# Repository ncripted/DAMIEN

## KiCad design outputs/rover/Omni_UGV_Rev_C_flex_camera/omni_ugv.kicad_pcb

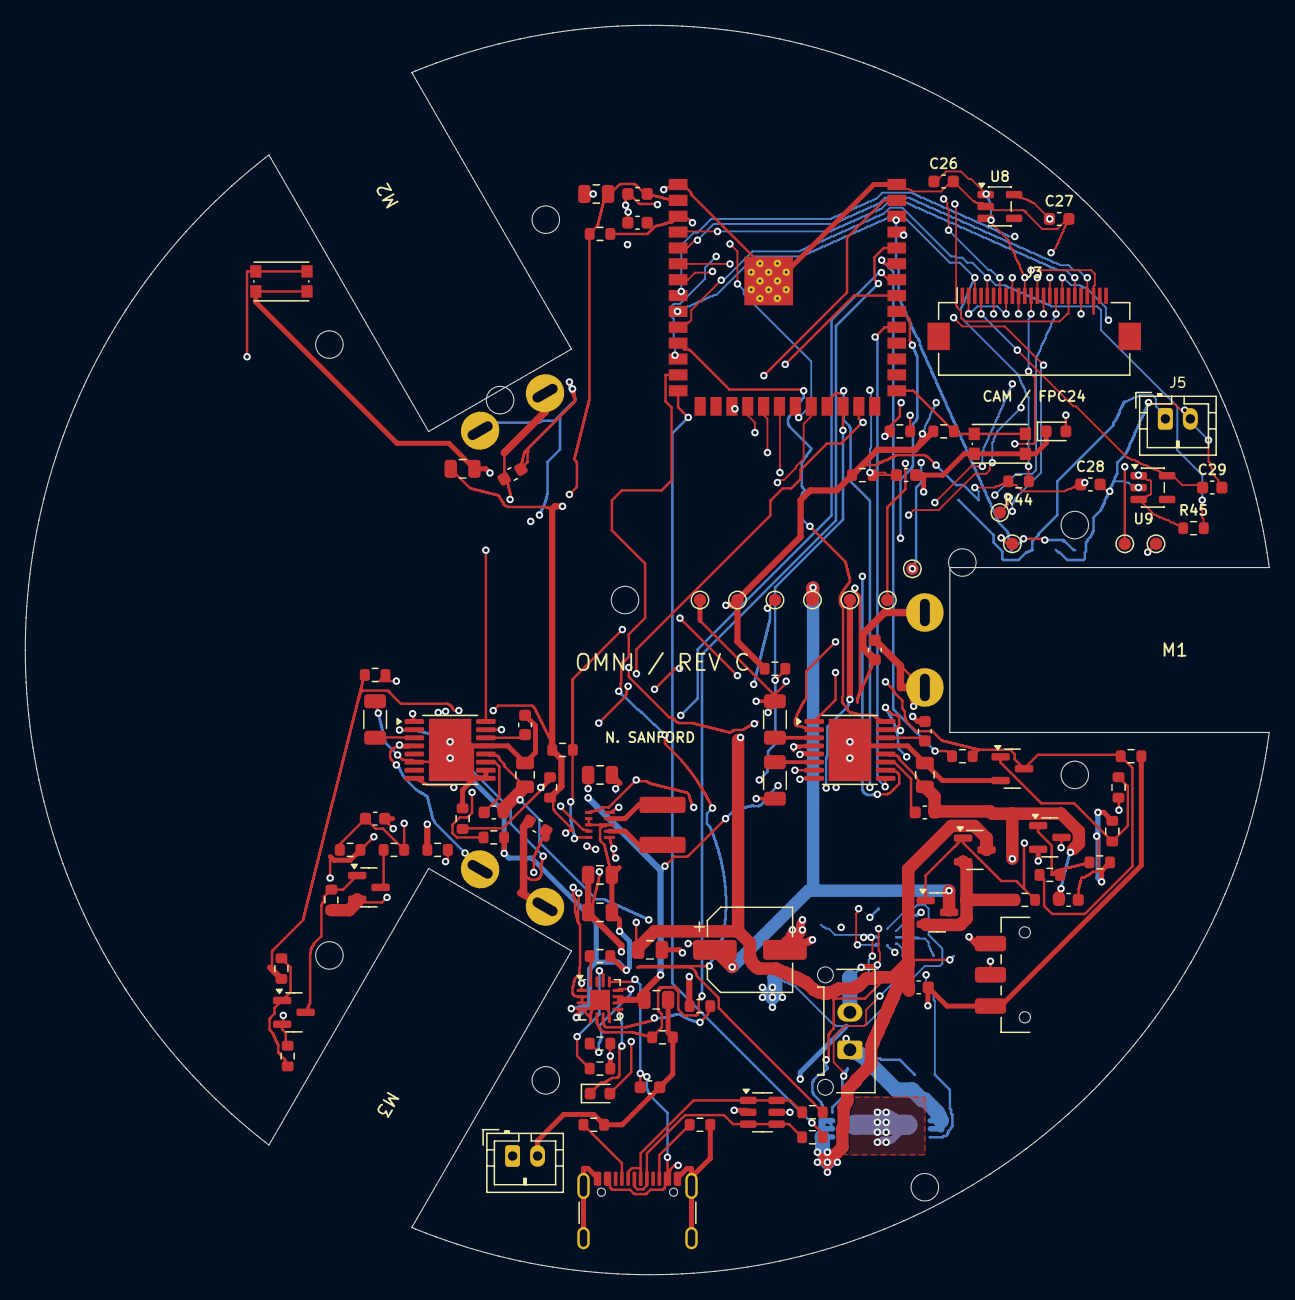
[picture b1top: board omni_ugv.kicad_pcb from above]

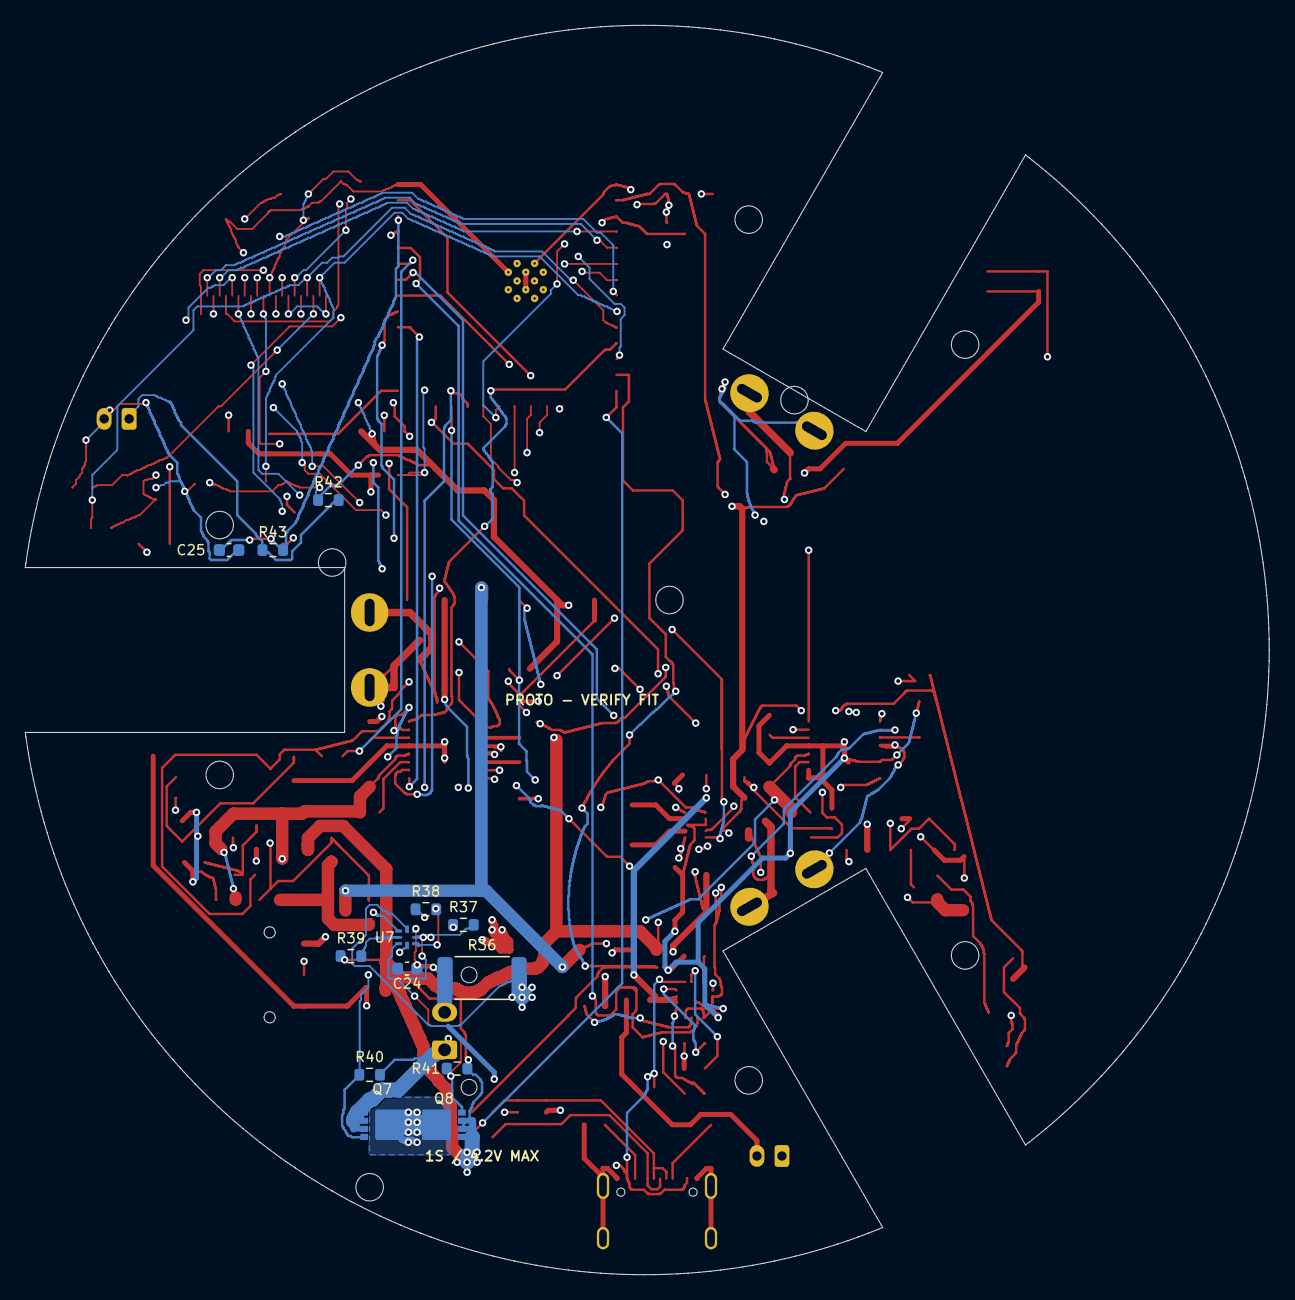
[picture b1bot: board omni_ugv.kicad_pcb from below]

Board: 4 copper layers, 99.6 x 100.0 mm, 127 parts (13 on the bottom side), 87 nets.

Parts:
C1, C15, C21: 1u/10V; Capacitor_SMD__C_0603_1608Metric
C2, C5, C6, C9, C16, C17, C18: 10u/10V; Capacitor_SMD__C_0805_2012Metric
C3, C4, C22, C23: 100n/16V; Capacitor_SMD__C_0603_1608Metric
C7, C10: 2.2u/10V; Capacitor_SMD__C_0603_1608Metric
C8, C11: 10n/25V; Capacitor_SMD__C_0603_1608Metric
C12, C13, C14: 100n/25V; Capacitor_SMD__C_0603_1608Metric
C19, C20: 22u/10V; Capacitor_SMD__C_0805_2012Metric
C24, C25: 100n/16V X7R; Capacitor_SMD__C_0603_1608Metric
C26, C27, C28, C29: 2.2u/10V X7R; Capacitor_SMD__C_0603_1608Metric
C90: 220u/10V; CP_Elec_6.3x5.8_HandAssembly
D1: STATUS GREEN; LED_SMD__LED_0603_1608Metric
D2: CHARGE AMBER; LED_SMD__LED_0603_1608Metric
H1, H2, H3, H4, H5, H6, H7, H8, H9, H10: M2; MountingHole_2.2mm_M2
J1: USB-C; Connector_USB__USB_C_Receptacle_GCT_USB4105-xx-A_16P_TopMnt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
J2: RAW 1S CELL 4.2V MAX; Connector_Molex__Molex_Micro-Fit_3.0_43650-0215_1x02_P3.00m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
J3: M0031 CAMERA FPC24; Camera_FH12_24
J4: CELL NTC - CHARGER; Connector_JST__JST_PH_B2B-PH-K_1x02_P2.00mm_Vertical
J5: CELL NTC - DRIVE; Connector_JST__JST_PH_B2B-PH-K_1x02_P2.00mm_Vertical
L1: 0.47uH/5.4A; L_XFL4015
M1: POLOLU 3065 MOTOR 1; Pololu_HPCB_Solder
M2: POLOLU 3065 MOTOR 2; Pololu_HPCB_Solder
M3: POLOLU 3065 MOTOR 3; Pololu_HPCB_Solder
Q1, Q2, Q5: AO3401A; Package_TO_SOT_SMD__SOT-23
Q3, Q4, Q6: MMBT3904; Package_TO_SOT_SMD__SOT-23
Q7, Q8: CSD17308Q3; CSD17308Q3_TI
R1, R2, R4, R5, R8, R29: 10k; Resistor_SMD__R_0603_1608Metric
R3, R27: 1k; Resistor_SMD__R_0603_1608Metric
R6, R7, R9: 0.25R/0.5W; Resistor_SMD__R_1206_3216Metric
R10, R11: 5.1k; Resistor_SMD__R_0603_1608Metric
R12, R13: 22R; Resistor_SMD__R_0603_1608Metric
R14: 3.57k; Resistor_SMD__R_0603_1608Metric
R15: 3.24k; Resistor_SMD__R_0603_1608Metric
R16: 46.4k; Resistor_SMD__R_0603_1608Metric
R17, R19, R22, R23, R24, R25, R26, R28, R30, R31, R33, R34, R35: 100k; Resistor_SMD__R_0603_1608Metric
R18: 2.2k; Resistor_SMD__R_0603_1608Metric
R20: 511k; Resistor_SMD__R_0603_1608Metric
R21: 91k; Resistor_SMD__R_0603_1608Metric
R32: 47k; Resistor_SMD__R_0603_1608Metric
R36: 10m 1% 1W; Resistor_SMD__R_2512_6332Metric
R37: 100R 1%; Resistor_SMD__R_0603_1608Metric
R38: 20R 1%; Resistor_SMD__R_0603_1608Metric
R39, R43: 1k 1%; Resistor_SMD__R_0603_1608Metric
R40, R41: 10M; Resistor_SMD__R_0603_1608Metric
R42: 10k 1%; Resistor_SMD__R_0603_1608Metric
R44, R45: 4.7k; Resistor_SMD__R_0603_1608Metric
SW1: RESET; Button_Switch_SMD__SW_Push_1P1T_NO_CK_KMR2
SW2: BOOT; Button_Switch_SMD__SW_Push_1P1T_NO_CK_KMR2
SW3: POWER; Button_Switch_SMD__SW_SPDT_CK_JS102011SAQN
TP1: GND; TestPoint__TestPoint_Pad_D1.0mm
TP2: +3V3; TestPoint__TestPoint_Pad_D1.0mm
TP3: VBAT; TestPoint__TestPoint_Pad_D1.0mm
TP4: VMOTOR; TestPoint__TestPoint_Pad_D1.0mm
TP5: SYS_RAW; TestPoint__TestPoint_Pad_D1.0mm
TP6: ESP_EN; TestPoint__TestPoint_Pad_D1.0mm
TP7: LED_STATUS; TestPoint__TestPoint_Pad_D1.0mm
TP8: DRIVE_ENABLE; TestPoint__TestPoint_Pad_D1.0mm
TP9: FAULT_U2; TestPoint__TestPoint_Pad_D1.0mm
TP10: FAULT_U3; TestPoint__TestPoint_Pad_D1.0mm
TP11: REG_PG; TestPoint__TestPoint_Pad_D1.0mm
U1: ESP32-S3-WROOM-1-N8R8; RF_Module__ESP32-S3-WROOM-1
U2, U3: DRV8833PWP; Package_SO__HTSSOP-16-1EP_4.4x5mm_P0.65mm_EP3.4x5mm_Mask2.4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
U4: TPS63802DLA; TPS63802_DLA0010A
U5: BQ24074RGT; Package_DFN_QFN__VQFN-16-1EP_3x3mm_P0.5mm_EP1.6x1.6mm
U6: USBLC6-2SC6; Package_TO_SOT_SMD__SOT-23-6
U7: BQ298217RUGR; BQ298217_RUG0008A
U8: TLV75513PDBVR; Camera_SOT23_5
U9: TLV75528PDBVR; Camera_SOT23_5

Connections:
+3V3: C2.1, C3.1, C5.1, C19.1, C20.1, C26.1, C28.1, J3.11, R1.1, R2.1, R4.1, R5.1, R8.1, R19.1, R20.1, R22.1, R32.1, R42.1, R44.1, R45.1, TP2.1, U1.2, U4.6, U8.1, U8.3, U9.1, U9.3
BAT_NTC: J4.1, U5.1
CAM_1V3: C27.1, J3.10, U8.5
CAM_2V8: C29.1, J3.4, U9.5
CAM_D0: J3.19, U1.4
CAM_D1: J3.21, U1.5
CAM_D2: J3.22, U1.6
CAM_D3: J3.20, U1.7
CAM_D4: J3.18, U1.12
CAM_D5: J3.16, U1.17
CAM_D6: J3.14, U1.18
CAM_D7: J3.12, U1.19
CAM_HREF: J3.9, U1.22
CAM_PCLK: J3.17, U1.20
CAM_RESET: C4.1, J3.6, R4.2
CAM_SCL: J3.5, R45.2, U1.10
CAM_SDA: J3.3, R44.2, U1.9
CAM_VSYNC: J3.7, U1.21
CAM_XCLK: J3.13, U1.8
CELL_N: C24.2, J2.2, R36.1, U7.3, U7.5
CELL_P: J2.1, Q7.1, Q7.2, Q7.3, R37.1, R38.1, R40.2
CELL_TEMP_ADC: C25.1, R43.2, U1.38
CELL_TEMP_DIV: J5.1, R42.2, R43.1
CHG_ILIM: R15.1, U5.12
CHG_ISET: R14.1, U5.16
CHG_LED_A: D2.2, R18.2
CHG_PGOOD: R19.2, U5.7
CHG_STATUS: D2.1, U5.9
CHG_TIMER: R16.1, U5.14
DRIVE_ENABLE: Q4.3, R25.1, R27.2, R28.1, TP8.1, U2.1, U3.1
DRIVE_REQ: R27.1, U1.35
ESP_BOOT: R2.2, SW2.1, U1.27
ESP_EN: C1.1, R1.2, SW1.1, TP6.1, U1.3
FAULT_U2: R5.2, TP9.1, U1.24, U2.8
FAULT_U3: R8.2, TP10.1, U1.25, U3.8
GND: C1.2, C2.2, C3.2, C4.2, C5.2, C6.2, C7.2, C9.2, C10.2, C15.2, C16.2, C17.2, C18.2, C19.2, C20.2, C21.2, C22.2, C23.2, C25.2, C26.2, C27.2, C28.2, C29.2, C90.2, D1.1, J1.A1, J1.A12, J1.B1, J1.B12, J1.S1, J3.2, J3.8, J3.15, J4.2, J5.2, Q3.2, Q4.2, Q6.2, R6.2, R7.2, R9.2, R10.2, R11.2, R14.2, R15.2, R16.2, R17.2, R21.2, R23.2, R26.2, R28.2, R30.2, R33.2, R35.2, R36.2, SW1.2, SW2.2, SW3.1, TP1.1, U1.1, U1.40, U1.41, U2.13, U2.17, U3.6, U3.9, U3.10, U3.13, U3.17, U4.2, U4.3, U4.8, U5.4, U5.5, U5.8, U5.17, U6.2, U7.4, U8.2, U9.2
LED_A: D1.2, R3.2
LED_STATUS: R3.1, TP7.1, U1.37
M1_A: C12.1, M1.1, U2.2
M1_B: C12.2, M1.2, U2.4
M1_IN1: U1.11, U2.16
M1_IN2: U1.23, U2.15
M1_SENSE: R6.1, U2.3
M2_A: C13.1, M2.1, U2.7
M2_B: C13.2, M2.2, U2.5
M2_IN1: U1.31, U2.9
M2_IN2: U1.32, U2.10
M2_SENSE: R7.1, U2.6
M3_A: C14.1, M3.1, U3.2
M3_B: C14.2, M3.2, U3.4
M3_IN1: U1.33, U3.16
M3_IN2: U1.34, U3.15
M3_SENSE: R9.1, U3.3
MEAS_BASE: Q6.1, R32.2, R33.1
MEAS_GATE: Q5.1, Q6.3, R31.2
MOTOR_BASE: Q3.1, R25.2, R26.1
MOTOR_GATE: Q1.1, Q2.1, Q3.3, R24.2
MOTOR_MID: Q1.2, Q2.2, R24.1
PROT_BAT: R38.2, U7.1
PROT_CHG: Q7.4, R40.1, U7.8
PROT_DRAIN: Q7.5, Q7.6, Q7.7, Q7.8, Q7.9, Q8.5, Q8.6, Q8.7, Q8.8, Q8.9
PROT_DSG: Q8.4, R41.1, U7.7
PROT_PACK: R39.2, U7.6
PROT_VDD: C24.1, R37.2, U7.2
REG_FB: R20.2, R21.1, U4.4
REG_L1: L1.1, U4.9
REG_L2: L1.2, U4.7
REG_PG: R22.2, TP11.1, U4.5
SYS_ON: R23.1, SW3.2, U4.1
SYS_RAW: C17.1, C18.1, R18.1, SW3.3, TP5.1, U4.10, U5.10, U5.11
U2_VCP: C8.1, U2.11
U2_VINT: C7.1, U2.14
U3_VCP: C11.1, U3.11
U3_VINT: C10.1, U3.14
USB_5V: C15.1, J1.A4, J1.A9, J1.B4, J1.B9, R29.1, U5.13, U6.5
USB_500_ENABLE: R17.1, U1.36, U5.6
USB_CC1: J1.A5, R10.1
USB_CC2: J1.B5, R11.1
USB_DETECT_BASE: Q4.1, R29.2, R30.1
USB_DM: R12.2, U1.13
USB_DM_EXT: J1.A7, J1.B7, R12.1, U6.1, U6.6
USB_DP: R13.2, U1.14
USB_DP_EXT: J1.A6, J1.B6, R13.1, U6.3, U6.4
VBAT: C16.1, C21.1, Q1.3, Q5.2, Q8.1, Q8.2, Q8.3, R31.1, R39.1, R41.2, TP3.1, U5.2, U5.3
VBAT_ADC: C23.1, R34.2, R35.1, U1.39
VBAT_MEAS: Q5.3, R34.1
VMOTOR: C6.1, C8.2, C9.1, C11.2, C22.1, C90.1, Q2.3, TP4.1, U2.12, U3.12

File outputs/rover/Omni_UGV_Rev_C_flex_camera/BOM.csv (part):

Reference,Value,MPN,Footprint,Notes
U1,ESP32-S3-WROOM-1-N8R8,ESP32-S3-WROOM-1-N8R8,UGV:RF_Module__ESP32-S3-WROOM-1,
R1,10k,,UGV:Resistor_SMD__R_0603_1608Metric,
C1,1u/10V,,UGV:Capacitor_SMD__C_0603_1608Metric,
R2,10k,,UGV:Resistor_SMD__R_0603_1608Metric,
C2,10u/10V,,UGV:Capacitor_SMD__C_0805_2012Metric,
C3,100n/16V,,UGV:Capacitor_SMD__C_0603_1608Metric,
SW1,RESET,KMR221GLFS,UGV:Button_Switch_SMD__SW_Push_1P1T_NO_CK_KMR2,
SW2,BOOT,KMR221GLFS,UGV:Button_Switch_SMD__SW_Push_1P1T_NO_CK_KMR2,
R3,1k,,UGV:Resistor_SMD__R_0603_1608Metric,
D1,STATUS GREEN,0603 green LED,UGV:LED_SMD__LED_0603_1608Metric,
R4,10k,,UGV:Resistor_SMD__R_0603_1608Metric,
C4,100n/16V,,UGV:Capacitor_SMD__C_0603_1608Metric,
C5,10u/10V,,UGV:Capacitor_SMD__C_0805_2012Metric,
U2,DRV8833PWP,DRV8833PWPR,UGV:Package_SO__HTSSOP-16-1EP_4.4x5mm_P0.65mm_EP3.4x5mm_Mask2.46x2.31mm,
C6,10u/10V,,UGV:Capacitor_SMD__C_0805_2012Metric,
C7,2.2u/10V,,UGV:Capacitor_SMD__C_0603_1608Metric,
C8,10n/25V,,UGV:Capacitor_SMD__C_0603_1608Metric,
R5,10k,,UGV:Resistor_SMD__R_0603_1608Metric,
R6,0.25R/0.5W,,UGV:Resistor_SMD__R_1206_3216Metric,
R7,0.25R/0.5W,,UGV:Resistor_SMD__R_1206_3216Metric,
U3,DRV8833PWP,DRV8833PWPR,UGV:Package_SO__HTSSOP-16-1EP_4.4x5mm_P0.65mm_EP3.4x5mm_Mask2.46x2.31mm,
C9,10u/10V,,UGV:Capacitor_SMD__C_0805_2012Metric,
C10,2.2u/10V,,UGV:Capacitor_SMD__C_0603_1608Metric,
C11,10n/25V,,UGV:Capacitor_SMD__C_0603_1608Metric,
R8,10k,,UGV:Resistor_SMD__R_0603_1608Metric,
R9,0.25R/0.5W,,UGV:Resistor_SMD__R_1206_3216Metric,
M1,POLOLU 3065 MOTOR 1,Pololu 3065,UGV:Pololu_HPCB_Solder,Terminal slots require physical fit check; use separate printed clamps
C12,100n/25V,,UGV:Capacitor_SMD__C_0603_1608Metric,
M2,POLOLU 3065 MOTOR 2,Pololu 3065,UGV:Pololu_HPCB_Solder,Terminal slots require physical fit check; use separate printed clamps
C13,100n/25V,,UGV:Capacitor_SMD__C_0603_1608Metric,
M3,POLOLU 3065 MOTOR 3,Pololu 3065,UGV:Pololu_HPCB_Solder,Terminal slots require physical fit check; use separate printed clamps
C14,100n/25V,,UGV:Capacitor_SMD__C_0603_1608Metric,
C90,220u/10V,Panasonic EEEFT1A221AP,UGV:CP_Elec_6.3x5.8_HandAssembly,"6.3mm diameter, 5.8mm high; oversized hand-assembly lands; approved 220-470uF bulk range; check actual PWM ripple"
J1,USB-C,GCT USB4105-GF-A,UGV:Connector_USB__USB_C_Receptacle_GCT_USB4105-xx-A_16P_TopMnt_Horizontal,
R10,5.1k,,UGV:Resistor_SMD__R_0603_1608Metric,
R11,5.1k,,UGV:Resistor_SMD__R_0603_1608Metric,
U6,USBLC6-2SC6,USBLC6-2SC6,UGV:Package_TO_SOT_SMD__SOT-23-6,
R12,22R,,UGV:Resistor_SMD__R_0603_1608Metric,
R13,22R,,UGV:Resistor_SMD__R_0603_1608Metric,
U5,BQ24074RGT,BQ24074RGTR,UGV:Package_DFN_QFN__VQFN-16-1EP_3x3mm_P0.5mm_EP1.6x1.6mm,
R14,3.57k,,UGV:Resistor_SMD__R_0603_1608Metric,
R15,3.24k,,UGV:Resistor_SMD__R_0603_1608Metric,
R16,46.4k,,UGV:Resistor_SMD__R_0603_1608Metric,
R17,100k,,UGV:Resistor_SMD__R_0603_1608Metric,
C15,1u/10V,,UGV:Capacitor_SMD__C_0603_1608Metric,
C16,10u/10V,,UGV:Capacitor_SMD__C_0805_2012Metric,
C17,10u/10V,,UGV:Capacitor_SMD__C_0805_2012Metric,
J2,RAW 1S CELL 4.2V MAX,Molex 43650-0215,UGV:Connector_Molex__Molex_Micro-Fit_3.0_43650-0215_1x02_P3.00mm_Vertical,"Raw cell input, pin1 positive; protection now onboard. Cell itself must support >=4A continuous / >=5A peak. No CELL_N-to-GND bypass."
J4,CELL NTC - CHARGER,JST B2B-PH-K-S,UGV:Connector_JST__JST_PH_B2B-PH-K_1x02_P2.00mm_Vertical,"Independent 103AT-2 probe bonded to cell; both leads isolated from cell terminals. Pin1 TS, pin2 system GND. Do not share with J5."
D2,CHARGE AMBER,,UGV:LED_SMD__LED_0603_1608Metric,
R18,2.2k,,UGV:Resistor_SMD__R_0603_1608Metric,
R19,100k,,UGV:Resistor_SMD__R_0603_1608Metric,
U4,TPS63802DLA,TPS63802DLAR,UGV:TPS63802_DLA0010A,
L1,0.47uH/5.4A,Coilcraft XFL4015-471MEC,UGV:L_XFL4015,
C18,10u/10V,,UGV:Capacitor_SMD__C_0805_2012Metric,
C19,22u/10V,,UGV:Capacitor_SMD__C_0805_2012Metric,
C20,22u/10V,,UGV:Capacitor_SMD__C_0805_2012Metric,
R20,511k,,UGV:Resistor_SMD__R_0603_1608Metric,
R21,91k,,UGV:Resistor_SMD__R_0603_1608Metric,
R22,100k,,UGV:Resistor_SMD__R_0603_1608Metric,
R23,100k,,UGV:Resistor_SMD__R_0603_1608Metric,
SW3,POWER,C&K JS102011SAQN,UGV:Button_Switch_SMD__SW_SPDT_CK_JS102011SAQN,
Q1,AO3401A,AO3401A,UGV:Package_TO_SOT_SMD__SOT-23,
Q2,AO3401A,AO3401A,UGV:Package_TO_SOT_SMD__SOT-23,
Q5,AO3401A,AO3401A,UGV:Package_TO_SOT_SMD__SOT-23,
Q3,MMBT3904,MMBT3904,UGV:Package_TO_SOT_SMD__SOT-23,
Q4,MMBT3904,MMBT3904,UGV:Package_TO_SOT_SMD__SOT-23,
Q6,MMBT3904,MMBT3904,UGV:Package_TO_SOT_SMD__SOT-23,
R24,100k,,UGV:Resistor_SMD__R_0603_1608Metric,
R25,100k,,UGV:Resistor_SMD__R_0603_1608Metric,
R26,100k,,UGV:Resistor_SMD__R_0603_1608Metric,
R27,1k,,UGV:Resistor_SMD__R_0603_1608Metric,
R28,100k,,UGV:Resistor_SMD__R_0603_1608Metric,
R29,10k,,UGV:Resistor_SMD__R_0603_1608Metric,
R30,100k,,UGV:Resistor_SMD__R_0603_1608Metric,
C21,1u/10V,,UGV:Capacitor_SMD__C_0603_1608Metric,
C22,100n/16V,,UGV:Capacitor_SMD__C_0603_1608Metric,
R31,100k,,UGV:Resistor_SMD__R_0603_1608Metric,
R32,47k,,UGV:Resistor_SMD__R_0603_1608Metric,
R33,100k,,UGV:Resistor_SMD__R_0603_1608Metric,
R34,100k,,UGV:Resistor_SMD__R_0603_1608Metric,
R35,100k,,UGV:Resistor_SMD__R_0603_1608Metric,
C23,100n/16V,,UGV:Capacitor_SMD__C_0603_1608Metric,
TP1,GND,,UGV:TestPoint__TestPoint_Pad_D1.0mm,
TP2,+3V3,,UGV:TestPoint__TestPoint_Pad_D1.0mm,
TP3,VBAT,,UGV:TestPoint__TestPoint_Pad_D1.0mm,
TP4,VMOTOR,,UGV:TestPoint__TestPoint_Pad_D1.0mm,
TP5,SYS_RAW,,UGV:TestPoint__TestPoint_Pad_D1.0mm,
TP6,ESP_EN,,UGV:TestPoint__TestPoint_Pad_D1.0mm,
TP7,LED_STATUS,,UGV:TestPoint__TestPoint_Pad_D1.0mm,GPIO43 status LED test point; UART0 TX no longer exposed. Programming remains native USB.
TP8,DRIVE_ENABLE,,UGV:TestPoint__TestPoint_Pad_D1.0mm,
TP9,FAULT_U2,,UGV:TestPoint__TestPoint_Pad_D1.0mm,
TP10,FAULT_U3,,UGV:TestPoint__TestPoint_Pad_D1.0mm,
TP11,REG_PG,,UGV:TestPoint__TestPoint_Pad_D1.0mm,
U7,BQ298217RUGR,BQ298217RUGR,UGV:BQ298217_RUG0008A,4.25V OV / 2.6V UV / 60mV OCD; exact suffix required; zero-volt charging disabled
Q7,CSD17308Q3,CSD17308Q3,UGV:CSD17308Q3_TI,30V NFET; common-drain pair; source pins1-3 gate4 drain5-9
Q8,CSD17308Q3,CSD17308Q3,UGV:CSD17308Q3_TI,30V NFET; common-drain pair; source pins1-3 gate4 drain5-9
R36,10m 1% 1W,WSL2512R0100FEA,UGV:Resistor_SMD__R_2512_6332Metric,"Current shunt, Kelvin sense endpoints. Nominal6A OCD; do not substitute resistance."
R37,100R 1%,,UGV:Resistor_SMD__R_0603_1608Metric,
R38,20R 1%,,UGV:Resistor_SMD__R_0603_1608Metric,
R39,1k 1%,,UGV:Resistor_SMD__R_0603_1608Metric,
C24,100n/16V X7R,,UGV:Capacitor_SMD__C_0603_1608Metric,
R40,10M,,UGV:Resistor_SMD__R_0603_1608Metric,Gate discharge path; <1uA loading at normal gate drive
R41,10M,,UGV:Resistor_SMD__R_0603_1608Metric,
J5,CELL NTC - DRIVE,B2B-PH-K-S,UGV:Connector_JST__JST_PH_B2B-PH-K_1x02_P2.00mm_Vertical,Second electrically isolated103AT-2 probe bonded to same cell; not shared with J4
R42,10k 1%,,UGV:Resistor_SMD__R_0603_1608Metric,
R43,1k 1%,,UGV:Resistor_SMD__R_0603_1608Metric,
C25,100n/16V X7R,,UGV:Capacitor_SMD__C_0603_1608Metric,
TH1,10k NTC 1% B25/85=3435K,103AT-2,OFFBOARD,Cell-bonded charger probe -> J4; separate insulated two-wire harness; strain relief; never attach to PCB as temperature proxy
TH2,10k NTC 1% B25/85=3435K,103AT-2,OFFBOARD,Cell-bonded drive monitoring probe -> J5; separate insulated two-wire harness; strain relief; never attach to PCB as temperature proxy
BAT1,1S 3.7V 1000mAh 20C PROVISIONAL,PHB1S100020CJST,OFFBOARD,Assumptions authorized 2026-11-06; 62x34x6mm UNVERIFIED for 20C pack; connector/polarity/wire and cell limits require qualification. See engineering/BATTERY_ASSUMPTIONS.md. External assembly item; not a PCB-mounted symbol.
J3,M0031 CAMERA FPC24,FH12-24S-0.5SH(55),UGV:Camera_FH12_24,Rev C camera redesign; qualification pending
U8,TLV75513PDBVR,TLV75513PDBVR,UGV:Camera_SOT23_5,Rev C camera redesign; qualification pending
U9,TLV75528PDBVR,TLV75528PDBVR,UGV:Camera_SOT23_5,Rev C camera redesign; qualification pending
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
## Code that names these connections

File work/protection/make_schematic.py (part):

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top=(base/'omni_ugv.kicad_sch').read_text(); topid=re.search(r'\(uuid ([^)]+)',top)[1]; sid=uid('sheet')
# Relabel ONLY the connector's two local wire labels on the charging sheet.
s=(base/'charging.kicad_sch').read_text()
s=s.replace('(global_label "VBAT" (shape bidirectional) (at 459.74 195.58','(global_label "CELL_P" (shape bidirectional) (at 459.74 195.58')
s=s.replace('(global_label "GND" (shape bidirectional) (at 459.74 198.12','(global_label "CELL_N" (shape bidirectional) (at 459.74 198.12')
s=s.replace('1S BATTERY 4.2V MAX','RAW 1S CELL 4.2V MAX').replace('PACK NTC 10k','CELL NTC - CHARGER')
s=s.rstrip()[:-1]+note('J2 is RAW CELL: no ground connection except through R36. J4 uses an electrically isolated two-wire sensor bonded to the CELL.',30,310)+')'
(root/'charging.kicad_sch').write_text(s)
by['J2']['nets']={'1':'CELL_P','2':'CELL_N'};by['J2']['value']='RAW 1S CELL 4.2V MAX'
by['J2']['note']='Raw cell input, pin1 positive; protection now onboard. Cell itself must support >=4A continuous / >=5A peak. No CELL_N-to-GND bypass.'
by['J4']['value']='CELL NTC - CHARGER';by['J4']['note']='Independent 103AT-2 probe bonded to cell; both leads isolated from cell terminals. Pin1 TS, pin2 system GND. Do not share with J5.'
# GPIO1/ADC1 becomes temperature input; LED moves to GPIO43, formerly UART TX.
s=(base/'controller.kicad_sch').read_text()
for a,z,t in reversed(list(blocks(s))):
 if t.startswith('(global_label "LED_STATUS"'):
  # Only the label at the ESP32 pin; R3 retains LED_STATUS.
  at=re.search(r'\(at ([\d.]+) ([\d.]+)',t)
  print('LED label location',at.groups())
# Find pin 38 world coordinate from embedded symbol then its attached wire/label.
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  if pt in xy:ends+=xy
ed=[]
for a,z,t in blocks(s):
 if t.startswith('(global_label "LED_STATUS"'):
  xy=tuple(map(float,re.search(r'\(at ([-\d.]+) ([-\d.]+)',t).groups()))
  if xy in ends:ed.append((a,z,t.replace('"LED_STATUS"','"CELL_TEMP_ADC"')))
assert len(ed)==1
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add('U7','BQ298217RUGR','BQ298217','BQ298217_RUG0008A',{1:'PROT_BAT',2:'PROT_VDD',3:'CELL_N',4:'GND',5:'CELL_N',6:'PROT_PACK',7:'PROT_DSG',8:'PROT_CHG'},70,65,109,126,'BQ298217RUGR','4.25V OV / 2.6V UV / 60mV OCD; exact suffix required; zero-volt charging disabled')
new[-1]['a']=180
for ref,src,gate,x,bx,ang in [('Q7','CELL_P','PROT_CHG',145,115,0),('Q8','VBAT','PROT_DSG',220,121,180)]:
 add(ref,'CSD17308Q3','CSD17308Q3','CSD17308Q3_TI',{i:src if i<4 else gate if i==4 else 'PROT_DRAIN' for i in range(1,10)},x,65,bx,138,'CSD17308Q3','30V NFET; common-drain pair; source pins1-3 gate4 drain5-9')
 new[-1]['a']=ang
add('R36','10m 1% 1W','Device__R','Resistor_SMD__R_2512_6332Metric',{1:'CELL_N',2:'GND'},55,115,113,127,'WSL2512R0100FEA','Current shunt, Kelvin sense endpoints. Nominal6A OCD; do not substitute resistance.')
add('R37','100R 1%','Device__R',R,{1:'CELL_P',2:'PROT_VDD'},105,115,106,126)
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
